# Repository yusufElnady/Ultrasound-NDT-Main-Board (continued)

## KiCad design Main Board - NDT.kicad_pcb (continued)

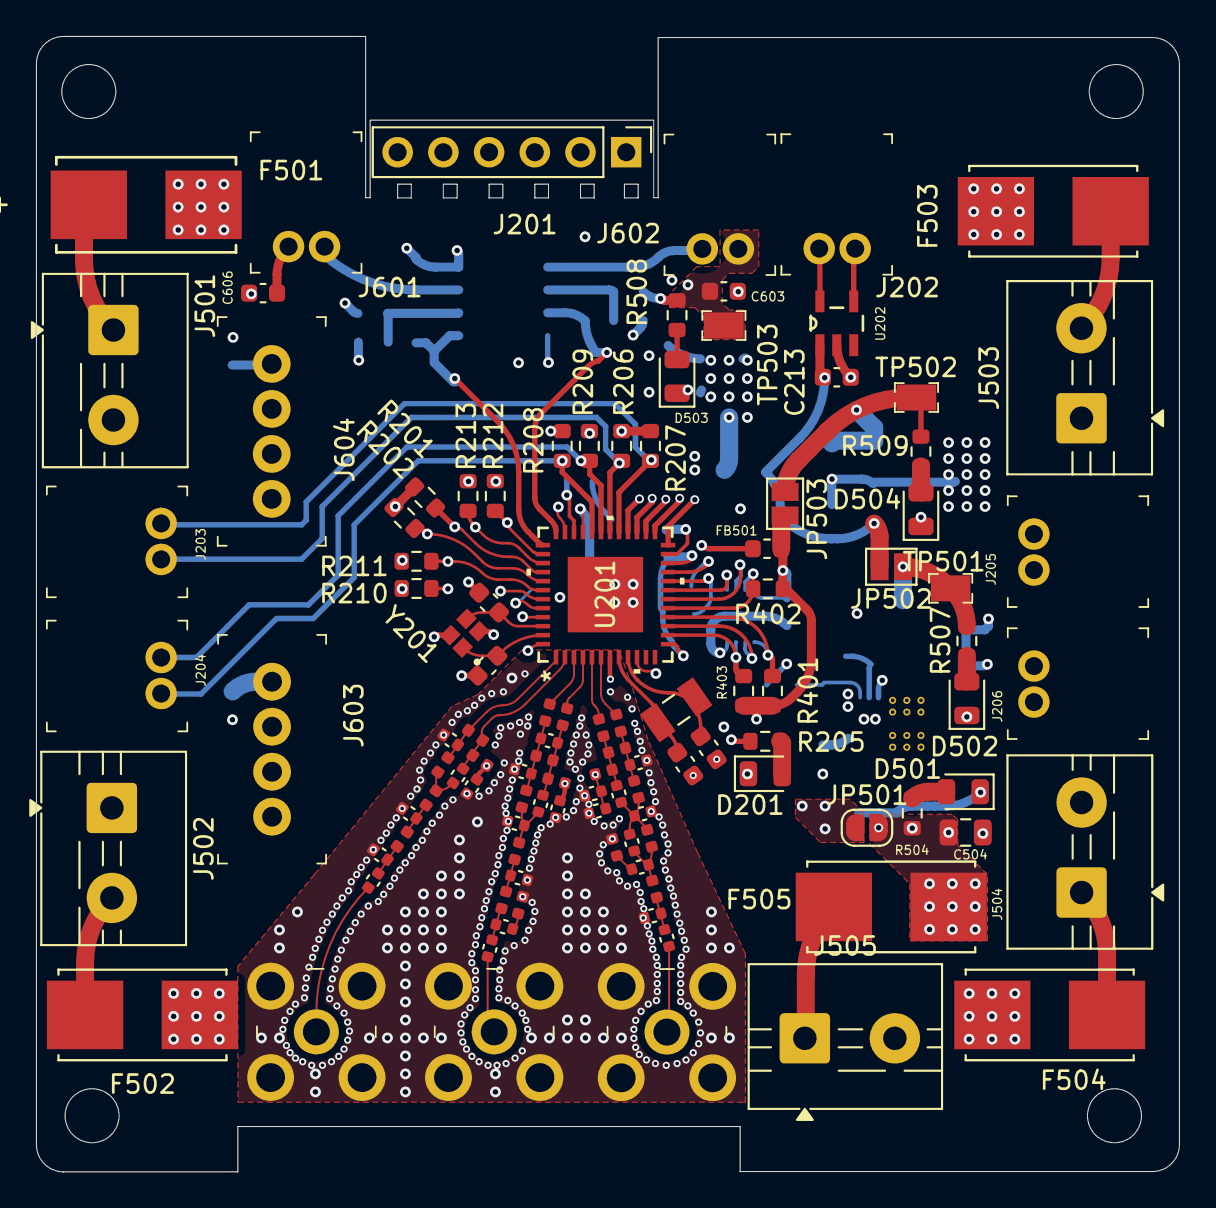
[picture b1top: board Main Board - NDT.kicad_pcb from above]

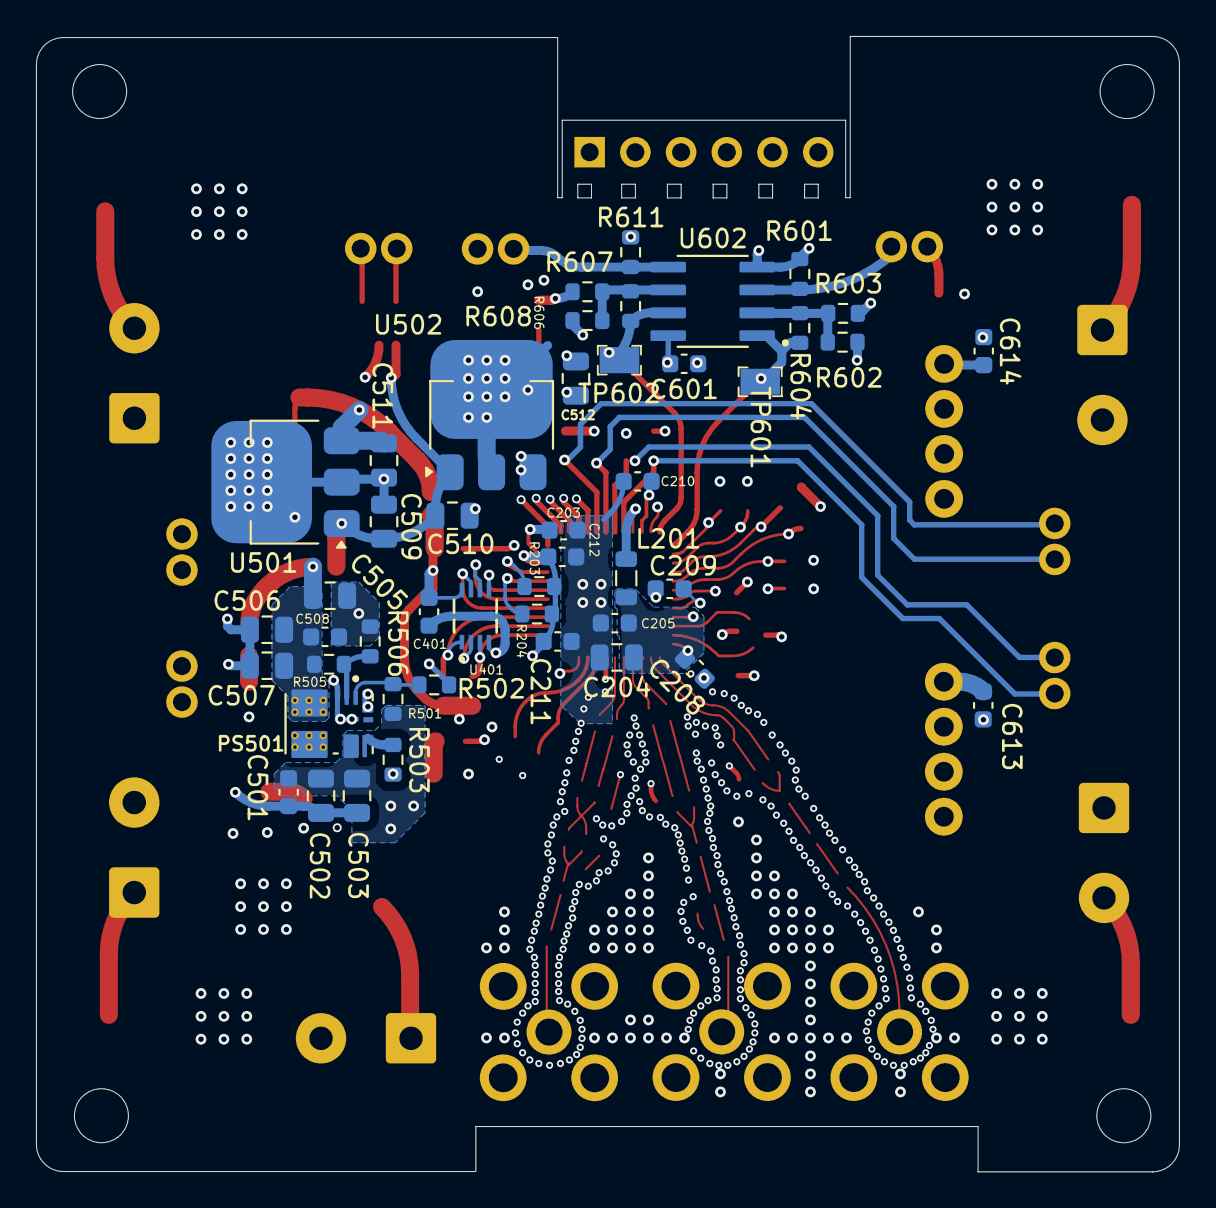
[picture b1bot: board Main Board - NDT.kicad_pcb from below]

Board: 6 copper layers, 63.5 x 63.1 mm, 155 parts (46 on the bottom side), 85 nets.

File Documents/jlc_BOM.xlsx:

Comment | Designator | Footprint | Quantity
4 pF | C201,C207 | Capacitor_SMD:C_0603_1608Metric | 2
22 pF | C202,C206 | Capacitor_SMD:C_0603_1608Metric | 2
1uF | C203,C209,C601,C603,C606,C613,C614 | Capacitor_SMD:C_0603_1608Metric | 7
22uF | C204,C505,C506,C507,C511,C512 | Capacitor_SMD:C_0805_2012Metric | 6
150pF | C205,C208 | Capacitor_SMD:C_0603_1608Metric | 2
100nF | C210,C211,C212,C213,C401,C501,C508 | Capacitor_SMD:C_0603_1608Metric | 7
1pF | C301,C305 | Capacitor_SMD:C_0402_1005Metric | 2
0.9pF | C302 | Capacitor_SMD:C_0402_1005Metric | 1
0.6pF | C303 | Capacitor_SMD:C_0402_1005Metric | 1
100pF | C304,C312,C315,C316,C322 | Capacitor_SMD:C_0402_1005Metric | 5
12pF | C306,C307 | Capacitor_SMD:C_0402_1005Metric | 2
3pF | C308,C309,C313 | Capacitor_SMD:C_0402_1005Metric | 3
7pF | C310 | Capacitor_SMD:C_0402_1005Metric | 1
3.9pF | C311,C321,C323 | Capacitor_SMD:C_0402_1005Metric | 3
2.6pF | C314 | Capacitor_SMD:C_0402_1005Metric | 1
2.4pF | C317,C318 | Capacitor_SMD:C_0402_1005Metric | 2
1.1pF | C319 | Capacitor_SMD:C_0402_1005Metric | 1
5.1pF | C320 | Capacitor_SMD:C_0402_1005Metric | 1
10uF | C502,C503,C504,C509,C510 | Capacitor_SMD:C_0805_2012Metric | 5
LED | D201,D501,D502,D503,D504 | LED_SMD:LED_0805_2012Metric | 5
015402.5DR | F501 | 015402.5DR:0154Series_LTF | 1
0154001.DR | F502,F503,F504,F505 | 0154001.DR:FUSE_0154001.DR | 4
1.5K 0.5A | FB501 | Inductor_SMD:L_0603_1608Metric | 1
6.8uH | L201 | Inductor_SMD:L_0805_2012Metric | 1
20nH | L301 | Inductor_SMD:L_0402_1005Metric | 1
3.7nH | L302,L303 | Inductor_SMD:L_0402_1005Metric | 2
3.4nH | L304,L311,L312 | Inductor_SMD:L_0402_1005Metric | 3
3.9nH | L305 | Inductor_SMD:L_0402_1005Metric | 1
10nH | L306,L308 | Inductor_SMD:L_0402_1005Metric | 2
22nH | L307 | Inductor_SMD:L_0402_1005Metric | 1
6.8nH | L309,L310 | Inductor_SMD:L_0402_1005Metric | 2
0.6nH | L313 | Inductor_SMD:L_0402_1005Metric | 1
1nH | L314,L315 | Inductor_SMD:L_0402_1005Metric | 2
12nH | L316,L318 | Inductor_SMD:L_0402_1005Metric | 2
27nH | L317 | Inductor_SMD:L_0402_1005Metric | 1
3nH | L319 | Inductor_SMD:L_0402_1005Metric | 1
5.1nH | L320 | Inductor_SMD:L_0402_1005Metric | 1
1.9nH | L321 | Inductor_SMD:L_0402_1005Metric | 1
TPSM84338RCJR | PS501 | TPSM84338RCJR:CONV_TPSM84338RCJR | 1
1k | R201,R202,R203,R204,R206,R207,R208,R209,R210,R211,R212,R213,R504 | Resistor_SMD:R_0603_1608Metric | 13
330R | R205,R508,R509 | Resistor_SMD:R_0603_1608Metric | 3
2.2K | R401,R402,R403 | Resistor_SMD:R_0603_1608Metric | 3
3k | R501 | Resistor_SMD:R_0603_1608Metric | 1
2k | R502 | Resistor_SMD:R_0603_1608Metric | 1
18k | R503 | Resistor_SMD:R_0603_1608Metric | 1
72.3k | R505 | Resistor_SMD:R_0603_1608Metric | 1
10k | R506 | Resistor_SMD:R_0603_1608Metric | 1
500R | R507 | Resistor_SMD:R_0603_1608Metric | 1
6.65k | R601,R611 | Resistor_SMD:R_0603_1608Metric | 2
1.91k | R602,R603,R607,R608 | Resistor_SMD:R_0603_1608Metric | 4
1.5k | R604,R606 | Resistor_SMD:R_0603_1608Metric | 2
CC1354P106T0RGZR | U201 | CC1354P106T0RGZR:VQFN48_RGZ_TEX | 1
LTC1694CS5TRMPBF | U202 | LTC1694CS5TRMPBF:SOT95P280X100-5N | 1
MX25R1635FZUIL0 | U401 | MX25R1635FZUIL0:USON-8L-2X3X0P6_MAC | 1
AZ1117CH2-3.3 | U501,U502 | Package_TO_SOT_SMD:SOT-223-3_TabPin2 | 2
TLV9002IDR | U602 | TLV9002IDR:SOIC127P599X175-8N | 1
ABM11W-48.0000MHZ-7-B1U-T3 | Y201 | ABM11W-48.0000MHZ-7-B1U-T3:XTAL_ABM11W-48.0000MHZ-7-B1U-T3 | 1
ABS07-32.768KHZ-T | Y202 | ABS07-32.768KHZ-T:XTAL_ABS07-32.768KHZ-T | 1

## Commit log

2026-04-20 replaced baluns with passives & wirewound inductors as recommended, PCB is ready for routing and fencing
2026-04-21 finished, just produce fabrication outputs
2026-04-28 added mounting holes and produced manufacturing files, ALL IS DONE Alhamdulillah
